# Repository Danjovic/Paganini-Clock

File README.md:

# Paganini-Clock
Wheel of time clock using 16 segment display and a Neopixel LED ring

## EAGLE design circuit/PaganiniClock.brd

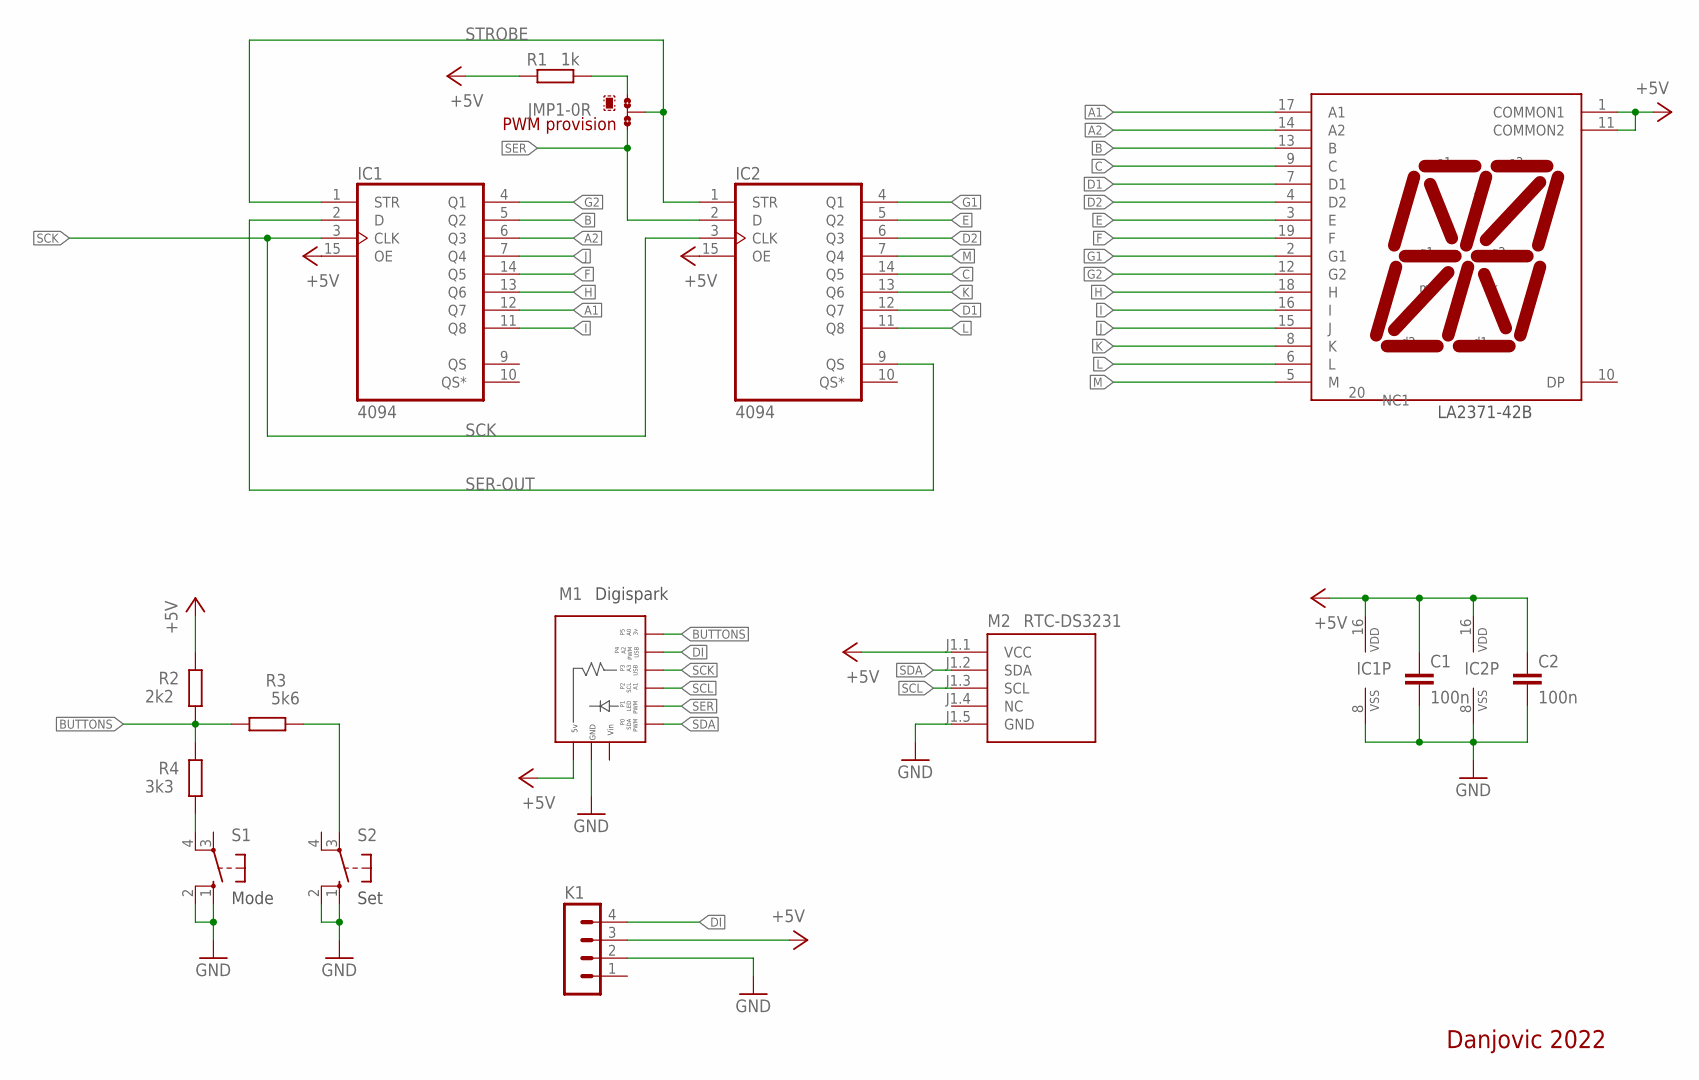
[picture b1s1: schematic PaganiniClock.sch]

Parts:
C1, C2: 100n; C050-024X044L
DS1: LA2371-42B; LA(C)2371-42B-M1
IC1, IC2: 4094; DIL16R
JMP1: DP_Option; B0R-JMP
K1: MA04-1
M1: Digispark; DIGISPARK_SOCKET
M2: RTC-DS3231; RTC-DS3231_SMALL
R1: 1k; 0204/7L
R2: 2k2; 0204/7L
R3: 5k6; 0204/7L
R4: 3k3; 0204/7L
S1, S2: 10-XX; B3F-10XX

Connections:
+5V: C1.1, C2.1, DS1.1 (COMMON1), DS1.11 (COMMON2), IC1.15 (OE), IC1.16 (VDD), IC2.15 (OE), IC2.16 (VDD), K1.3, M1.5V, M2.J1.1 (VCC), R1.2, R2.2
A1: DS1.17 (A1), IC1.12 (Q7)
A2: DS1.14 (A2), IC1.6 (Q3)
B: DS1.13 (B), IC1.5 (Q2)
BUTTONS: M1.P5, R2.1, R3.2, R4.2
C: DS1.9 (C), IC2.14 (Q5)
D1: DS1.7 (D1), IC2.12 (Q7)
D2: DS1.4 (D2), IC2.6 (Q3)
DI: K1.4, M1.P4
E: DS1.3 (E), IC2.5 (Q2)
F: DS1.19 (F), IC1.14 (Q5)
G1: DS1.2 (G1), IC2.4 (Q1)
G2: DS1.12 (G2), IC1.4 (Q1)
GND: C1.2, C2.2, IC1.8 (VSS), IC2.8 (VSS), K1.2, M1.GND, M2.J1.5 (GND), S1.1 (S), S1.2 (S1), S2.1 (S), S2.2 (S1)
H: DS1.18 (H), IC1.13 (Q6)
I: DS1.16 (I), IC1.11 (Q8)
J: DS1.15 (J), IC1.7 (Q4)
K: DS1.8 (K), IC2.13 (Q6)
L: DS1.6 (L), IC2.11 (Q8)
M: DS1.5 (M), IC2.7 (Q4)
unnamed: JMP1.1, R1.1
unnamed: R3.1, S2.3
unnamed: R4.1, S1.4 (P1)
SCK: IC1.3 (CLK), IC2.3 (CLK), M1.P3
SCL: M1.P2, M2.J1.3 (SCL)
SDA: M1.P0, M2.J1.2 (SDA)
SER: IC2.2 (D), JMP1.3, M1.P1
SER-OUT: IC1.2 (D), IC2.9 (QS)
STROBE: IC1.1 (STR), IC2.1 (STR), JMP1.2
VIN: M1.VIN

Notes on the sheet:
Mode
Set
Digispark
LA2371-42B
Danjovic 2022
PWM provision

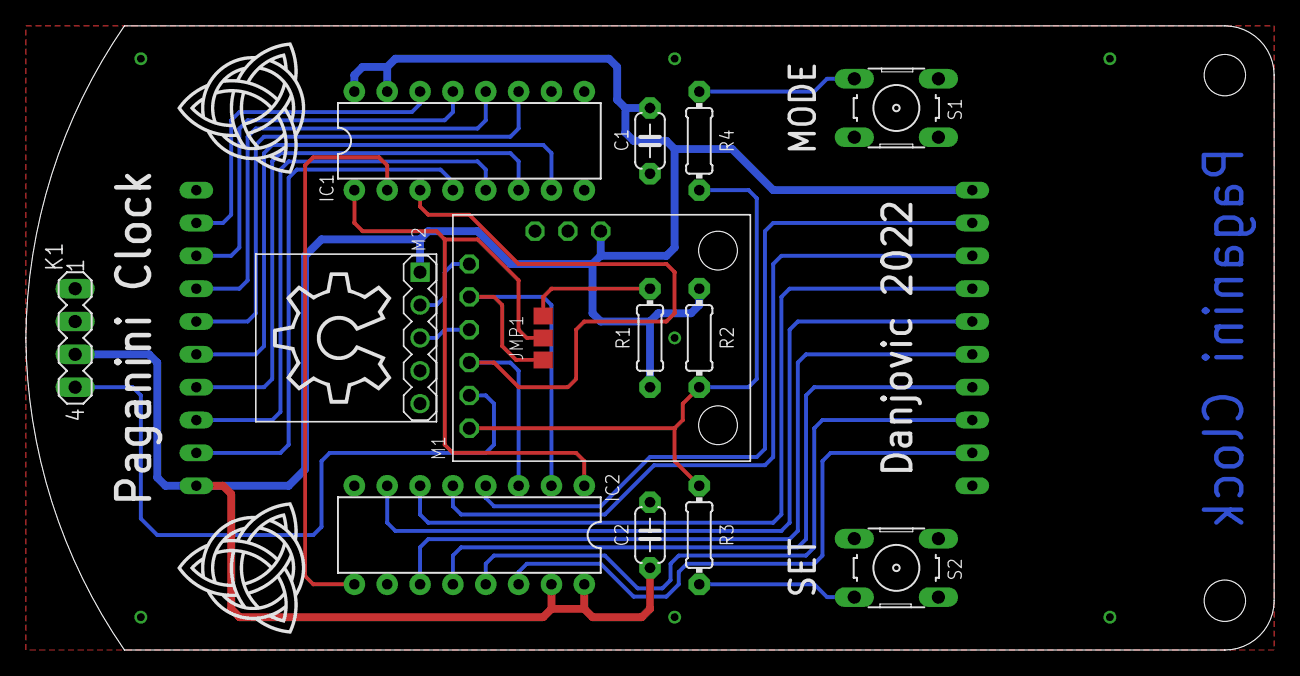
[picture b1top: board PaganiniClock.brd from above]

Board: 2 copper layers, 96.5 x 48.3 mm, 15 parts (1 on the bottom side), 29 nets.

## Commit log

2022-09-02 added ultradian mode with/without season
2022-09-02 added ultradian mode with/without season(2)
2022-09-03 fixed and enhanced 12 Hour clock mode on Led Ring
    //displays time considering 12 hours for full circle
    // from 06:00 to 17:59 hour is indicated by yellow led (sun is yellow)
    // from 18:00 to 05:59 hour is indicated by blue led (night hues are blueish)
    // every 2m30s interval is displayed using blinking red. 1 hour takes a full cycle
    // blinking rate is 1Hz, 50%
    // intersections are green for day time (AM) and magenta for night time (PM)
